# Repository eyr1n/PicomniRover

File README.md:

# PicomniRover サポートリポジトリ

## 目次

- [これは何？](#これは何)
- [購入するものリスト](#購入するものリスト)
  - [秋月電子通商で購入可能なもの](#秋月電子通商で購入可能なもの)
  - [ロボットショップで購入可能なもの](#ロボットショップで購入可能なもの)
  - [モノタロウで購入可能なもの](#モノタロウで購入可能なもの)
- [3Dプリント部品について](#3dプリント部品について)
- [基板について](#基板について)
- [ライセンス](#ライセンス)

## これは何？

本リポジトリは、コミックマーケット107にて頒布した「やる気出ないんズ 活動報告書 vol.1」内の「かんたん！全方位移動ロボットのつくりかた」にて製作する全方位移動ロボット「PicomniRover」に関する情報をまとめたリポジトリです。

## 購入するものリスト

ここでは、購入する必要のある市販の部品についてまとめます。私が使用した購入先は以下の3つです。

- [秋月電子通商 - https://akizukidenshi.com/](https://akizukidenshi.com/)
- [ロボットショップ(ヴイストン) - https://www.vstone.co.jp/robotshop/](https://www.vstone.co.jp/robotshop/)
- [モノタロウ - https://www.monotaro.com/](https://www.monotaro.com/)

すべてオンライン購入を前提に記載していますが、ねじ類などは近所のホームセンターでも代替可能です。必要に応じて入手しやすい手段を選んでいただければと思います。

また、同人誌内で製作するロボットの動作には、単3形の充電式ニッケル水素電池(公称1.2V)が6本必要です。Panasonic製eneloopやSony製CycleEnergyなど、単3形で公称電圧1.2Vの充電式ニッケル水素電池を用意してください。1.5Vのアルカリ乾電池は使用しないでください。

### 秋月電子通商で購入可能なもの

| 商品名 | 数量(使用数) | 単価(購入単位) | 購入リンク |
| --- | --- | --- | --- |
| Raspberry Pi Pico W | 1個 | ¥1,200 | [リンク](https://akizukidenshi.com/catalog/g/g117947) | 
| BNO055使用 9軸センサーフュージョンモジュールキット/AE-BNO055-BO | 1個 | ¥2,450 | [リンク](https://akizukidenshi.com/catalog/g/g116996) | 
| FEETECHシリアルバスサーボ STS3215 7.4V 14.4kg・cm 1:147 | 3個 | ¥2,780 | [リンク](https://akizukidenshi.com/catalog/g/g131132) | 
| 超高効率DCDCコンバーター(3.3V 0.5A) M78AR033-0.5 | 1個 | ¥380 | [リンク](https://akizukidenshi.com/catalog/g/g107178) | 
| 電池ボックス 単3×3本 リード線/BH-331-3A | 2個 | ¥70 | [リンク](https://akizukidenshi.com/catalog/g/g102667) | 
| XT30コネクター オス 基板取付用 XT30PW-M | 1個 | ¥70 | [リンク](https://akizukidenshi.com/catalog/g/g117949) | 
| XT30コネクター メス XT30U-F | 1個 | ¥50 | [リンク](https://akizukidenshi.com/catalog/g/g117950) | 
| Pch MOSFET 2SJ496TZ-E (60V 5A) | 1個 | ¥90 | [リンク](https://akizukidenshi.com/catalog/g/g109040) | 
| 電解コンデンサー 100μF 25V 105℃ ルビコンPX/25PX100MEFC5X11 | 1個 | ¥10 | [リンク](https://akizukidenshi.com/catalog/g/g117877) | 
| 積層セラミックコンデンサー 3.3μF 50V X7R 5mm/RDER71H335K3K1H03B | 1個 | ¥50 | [リンク](https://akizukidenshi.com/catalog/g/g108153) | 
| カーボン抵抗(炭素皮膜抵抗) 1/4W 1kΩ/CF25J1KB | 1本 (100本/袋) | ¥100 | [リンク](https://akizukidenshi.com/catalog/g/g125102) | 
| カーボン抵抗(炭素皮膜抵抗) 1/4W 3.3kΩ/CF25J3K3B | 2本 (100本/袋) | ¥140 | [リンク](https://akizukidenshi.com/catalog/g/g125332) | 
| ピンヘッダー 1×40 (40P)/PH-1x40SG | 2個 | ¥35 | [リンク](https://akizukidenshi.com/catalog/g/g100167) | 
| ピンヘッダー (L型) 1×6 (6P)/PH-1X6RG(2) | 1個 | ¥10 | [リンク](https://akizukidenshi.com/catalog/g/g105336) | 
| 分割ロングピンソケット 1×42 (42P)/FHU-1x42SG | 2個 | ¥80 | [リンク](https://akizukidenshi.com/catalog/g/g105779) | 
| 合計 |  | ¥13,260 |  | 

### ロボットショップで購入可能なもの

| 商品名 | 数量(使用数) | 単価(購入単位) | 購入リンク |
| --- | --- | --- | --- |
| 48mmオムニホイール(六角ハブ対応)(14038) | 3個 | ¥715 | [リンク](https://www.vstone.co.jp/robotshop/index.php?main_page=product_info&products_id=5180) | 
| 合計 |  | ¥2,145 |  | 

### モノタロウで購入可能なもの

| 商品名 | 数量(使用数) | 単価(購入単位) | 購入リンク |
| --- | --- | --- | --- |
| 六角穴付ボルト(ステンレス) 全ねじ M3×10mm | 6個 | ¥681 (55個/袋) | [リンク](https://www.monotaro.com/p/2901/7714/) | 
| 六角穴付ボルト(ステンレス) 全ねじ M3×12mm | 4個 | ¥802 (54個/袋) | [リンク](https://www.monotaro.com/p/2901/7723/) | 
| 六角穴付ボルト(ステンレス) 全ねじ M3×30mm | 3個 | ¥659 (25個/袋) | [リンク](https://www.monotaro.com/p/6891/0652/) | 
| 六角ナット1種 ステンレス M3 | 14個 | ¥175 (50個/袋) | [リンク](https://www.monotaro.com/p/2876/3448/) | 
| 平ワッシャー ステンレス M3×8×0.5 | 6個 | ¥99 (50個/袋) | [リンク](https://www.monotaro.com/p/2876/4114/) | 
| 合計 |  | ¥2,416 |  | 

## 3Dプリント部品について

ここでは、3Dプリンターで印刷する必要のある部品についてまとめます。ここで紹介する部品は、C107にて頒布した「ロボット部品セット」を購入した場合、印刷不要です。

印刷に使用した環境は以下の通りです。

- プリンター: Bambu Lab A1 mini
- ノズル径: 0.4mm
- プリセット: 0.20mm Standard @BBL A1M
- フィラメント: eSUN PLA+

| 部品名 | STEPファイル | 数量 | 備考 |
| --- | --- | --- | --- |
| ボディー | [STEP/body.step](STEP/body.step) | 1個 | 1層目のみ30mm/sで印刷 | 
| モーター固定具 | [STEP/motor_bracket.step](STEP/motor_bracket.step) | 3個 |  | 
| ホイール固定具1 | [STEP/wheel_mount1.step](STEP/wheel_mount1.step) | 3個 |  | 
| ホイール固定具2 | [STEP/wheel_mount2.step](STEP/wheel_mount2.step) | 3個 |  | 
| 基板スペーサー | [STEP/pcb_spacer.step](STEP/pcb_spacer.step) | 4個 |  | 

## 基板について

同人誌内で使用するシールド基板は KiCad 9.0.6 で設計し、JLCPCB に製造を発注しました。

プロジェクトファイル一式は [KiCad/PicomniRover](KiCad/PicomniRover) (`PicomniRover.kicad_pro` / `.kicad_pcb` / `.kicad_sch`) にあり、製造用ガーバーデータは [KiCad/PicomniRover/jlcpcb/production_files/GERBER-PicomniRover.zip](KiCad/PicomniRover/jlcpcb/production_files/GERBER-PicomniRover.zip) にまとめています。

回路図は以下の通りです。

## ライセンス

MIT ライセンス

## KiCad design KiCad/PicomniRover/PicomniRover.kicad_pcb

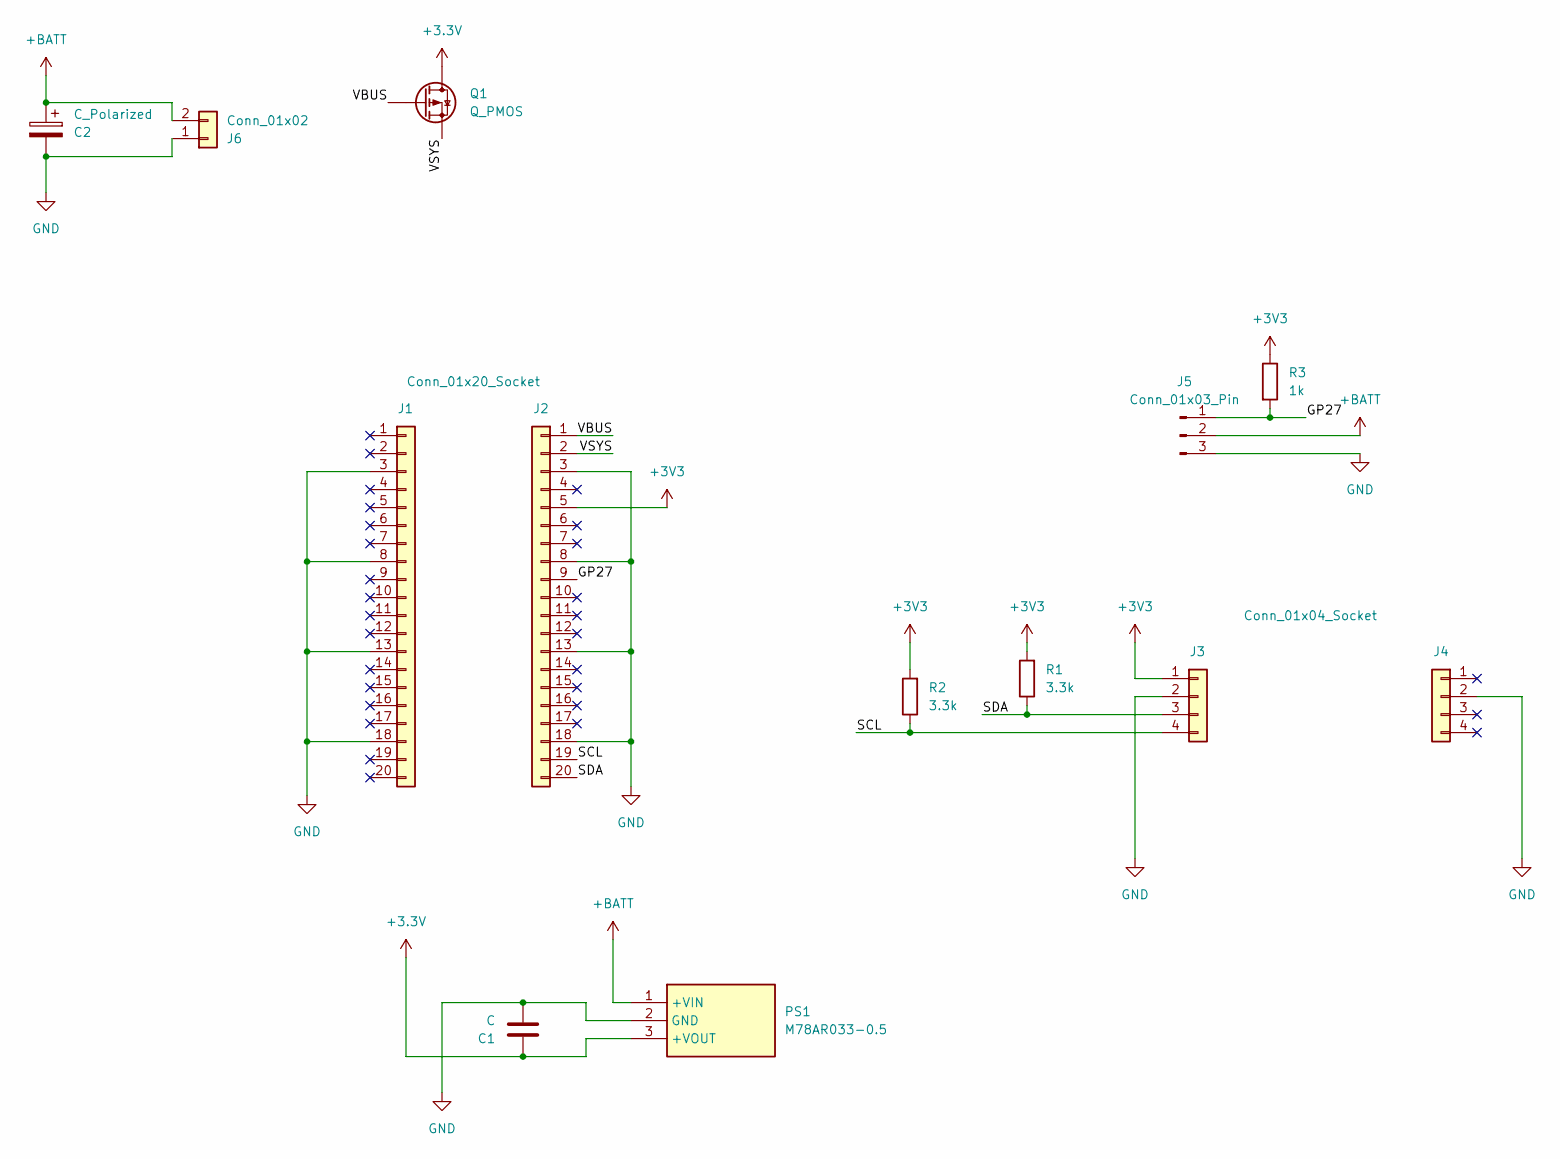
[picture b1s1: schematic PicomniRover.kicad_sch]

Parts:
C1: C; C_Disc_D5.0mm_W2.5mm_P5.00mm
C2: C_Polarized; CP_Radial_D6.3mm_P2.50mm
J1, J2: Conn_01x20_Socket; PinSocket_1x20_P2.54mm_Vertical
J3, J4: Conn_01x04_Socket; PinSocket_1x04_P2.54mm_Vertical
J5: Conn_01x03_Pin; PinHeader_1x03_P2.54mm_Horizontal
J6: Conn_01x02; AMASS_XT30PW-M_1x02_P2.50mm_Horizontal
PS1: M78AR033-0.5; M78AR03305; Manufacturer_Part_Number M78AR033-0.5
Q1: Q_PMOS; TO-92_Inline_Wide
R1, R2: 3.3k; R_Axial_DIN0207_L6.3mm_D2.5mm_P7.62mm_Horizontal
R3: 1k; R_Axial_DIN0207_L6.3mm_D2.5mm_P7.62mm_Horizontal

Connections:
+3.3V: C1.1, PS1.3 (+VOUT), Q1.2 (D)
+3V3: J2.5, J3.1, R1.2, R2.2, R3.1
+BATT: C2.1, J5.2, J6.2, PS1.1 (+VIN)
/GP27: J2.9, J5.1, R3.2
/SCL: J2.19, J3.4, R2.1
/SDA: J2.20, J3.3, R1.1
/VBUS: J2.1, Q1.3 (G)
/VSYS: J2.2, Q1.1 (S)
GND: C1.2, C2.2, J1.3, J1.8, J1.13, J1.18, J2.3, J2.8, J2.13, J2.18, J3.2, J4.2, J5.3, J6.1, PS1.2 (GND)

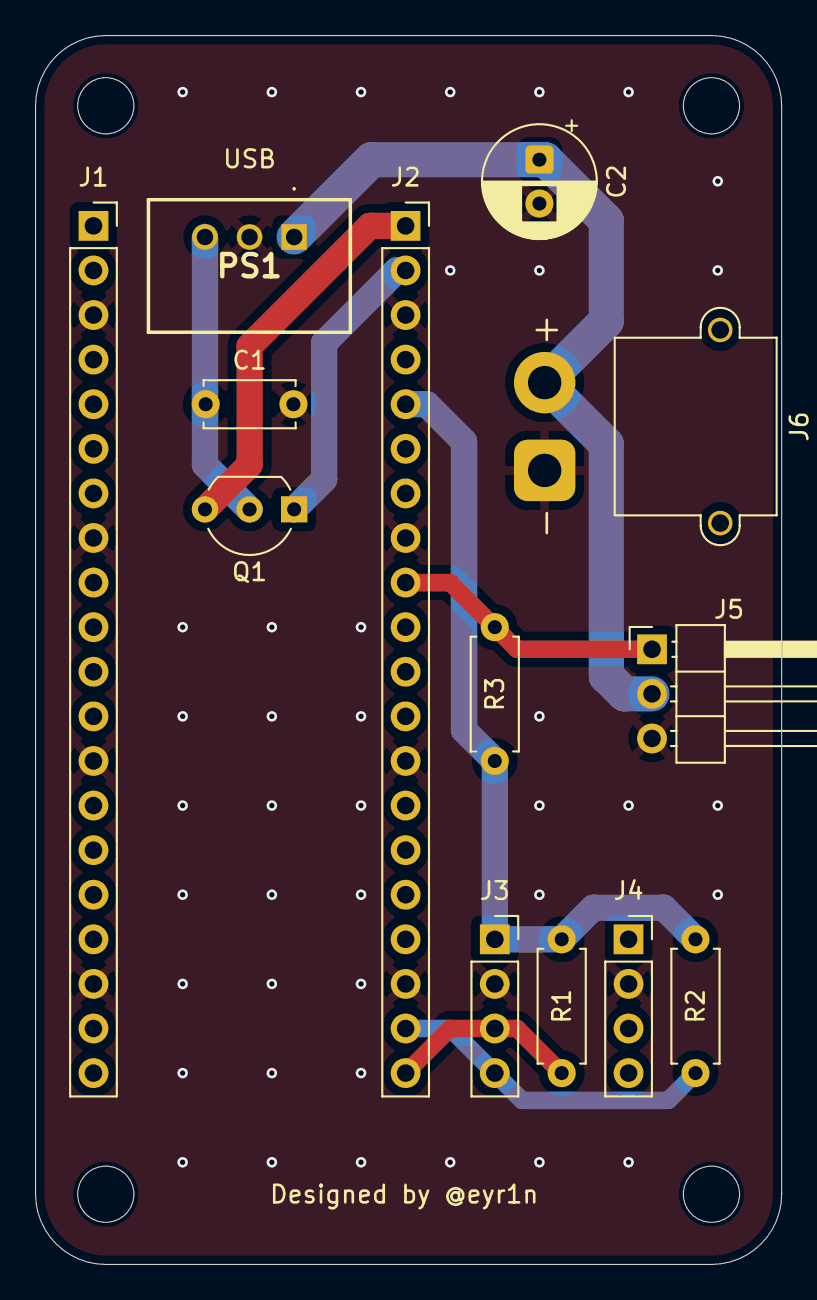
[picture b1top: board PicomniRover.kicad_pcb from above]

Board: 2 copper layers, 42.5 x 70.0 mm, 13 parts (0 on the bottom side), 9 nets.

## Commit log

2025-12-25 init
2025-12-30 いろいろ書いた
2025-12-30 Add MIT License to the project
2025-12-30 電池について
